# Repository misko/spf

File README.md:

# SPF (Signal Processing Fun)

## Youtube explanation

[Overview](https://www.youtube.com/watch?v=vj99KvB2AcA)

[Wall array v1 video](https://youtu.be/ljlRKGjBUoE) and [design+data+files](data_collection/2d_wall_array/2d_wall_array_v1)

[Wall array v2 video](https://youtu.be/9S3mgBD47kw) and [design+data+files](data_collection/2d_wall_array/2d_wall_array_v2)

[Rover v1 video](https://youtu.be/aGzOBduHrvo) and [design+data+files](data_collection/rover/rover_v1)

[Rover v2 video](https://youtube.com/shorts/qZmtBzATahE?feature=share) and [design+data+files](data_collection/rover/rover_v2)

Rover v3.1 [design+data+files](data_collection/rover/rover_v3.1)

## Problem statement:

Given a mobile radio receiver (agent/detector) find the optimal (minimal) path of movement to accurately locate physical radio emitters in the operating space

*(top left): The physical X,Y location of 3 static (non-mobile) emitters and one mobile detector (radio receiver). (top right): The raw radio signal from each antenna in the receiver radio array is [processed](spf/notebooks/03_beamformer_wNoise.ipynb) to produce a mapping from angle of incidence to signal strength. The larger the signal strength the more likely the signal originated from the corresponding angle. (bottom left): The ground truth the detector should output over enough time has elapsed. This represents the probability of finding an emitter at any X/Y coordinate. (bottom right): The processed radio signal from (top right) mapped into an image centered around the detectors position.*

## Background:

### The Challenge of Drone Detection

Detecting and locating small drones is increasingly important for security and airspace management. Traditional detection methods face significant challenges:

- Modern drones are small and becoming smaller
- Drones are often made from materials that don't reflect radar effectively
- Their extreme mobility makes tracking difficult with conventional systems

Most drones rely on radio frequency (RF) signals to communicate with operators, transmitting telemetry data and receiving commands. This RF communication provides an opportunity for detection even when visual or radar methods fail.

### Project Approach

This project develops optimal control algorithms for mobile radio receivers to locate RF emitters (such as drones) in an operational area. Key aspects of our approach:

1. **Mobile Detection**: Using airborne or ground-based mobile radio receivers that can dynamically position themselves for optimal signal reception
2. **Signal Integration**: Combining multiple signal measurements over time to build accurate emitter location maps
3. **Path Optimization**: Finding minimal movement paths that maximize information gain about emitter locations

### Technical Implementation

The system works by collecting and processing RF signals over time:

- **Signal Snapshots**: The receiver captures radio signals at discrete time intervals (snapshots)
- **Beamforming**: Raw antenna array data is processed through a [beamformer](spf/notebooks/03_beamformer_wNoise.ipynb) to map signal strength to angle of incidence
- **Spatial Mapping**: Processed signals are projected into a 2D probability map centered on the detector
- **Integration**: Multiple snapshots are combined to improve accuracy and reduce noise

The example below shows a single snapshot from our system. The blue circle represents the detector's position (with its path shown as a tail), while red circles mark emitter locations. The yellow areas in the bottom right image indicate high probability regions where an emitter is likely located based on the current signal processing.

## Current Progress

### Signal Processing & Algorithms

The project has implemented several sophisticated algorithms for emitter detection and localization:

#### Filtering Techniques
- **Extended Kalman Filters (EKF)**: Multiple implementations available in `spf/filters/`:
  - Single radio configuration (`ekf_single_radio_filter.py`)
  - Dual radio setup for improved accuracy (`ekf_dualradio_filter.py`)
  - XY coordinate tracking variants (`ekf_dualradioXY_filter.py`)

- **Particle Filters**: Probabilistic approach for robust tracking in noisy environments:
  - Single and dual radio implementations (`particle_single_radio_filter.py`, `particle_dualradio_filter.py`)
  - Neural network enhanced variants (`particle_single_radio_nn_filter.py`, `particle_dual_radio_nn_filter.py`)
  - XY coordinate variants for direct position estimation (`particle_dualradioXY_filter.py`)

#### Motion Planning
- Path planning algorithms in `spf/motion_planners/`:
  - Vehicle dynamics modeling (`dynamics.py`)
  - Optimal trajectory planning (`planner.py`)

#### Neural Network Models
- Advanced deep learning architectures in `spf/model_training_and_inference/models/`:
  - Point-based networks for signal processing (`single_point_networks.py`)
  - Optimized inference implementations (`single_point_networks_inference.py`) 
- Multiple model configurations in the `model_configs/` directory with variations in:
  - Network architecture (single vs. paired)
  - Regularization techniques (dropout, weight decay)
  - Training strategies (data augmentation, normalization)

### Data Collection & Hardware

#### Data Collection Systems
- **Wall-mounted Arrays**:
  - Fixed position antenna arrays for controlled experiments
  - Multiple versions (v1, v2) with different configurations

- **Mobile Platforms**:
  - Rover-based systems for dynamic data collection (v1, v2, v3.1)
  - Movement controlled via GRBL (`spf/grbl/`) or MAVLink (`spf/mavlink/`)
  - Flying drone platforms in experimental phase

#### Hardware Integration
- **SDR Support**:
  - **PlutoSDR** integration (`spf/sdrpluto/sdr_controller.py`)
  - **BladeRF 2.0** integration (`spf/sdrpluto/sdr_controller.py` with the `BladeRFSdr` class)
    - Advanced register-level configurations for phase alignment between channels
    - Support for multiple receivers with serial number identification
  - Signal processing and detrending utilities (`detrend.py`)
  - Abstracted hardware interfaces that work across SDR platforms

- **GPS Integration**:
  - Geolocation utilities (`spf/gps/gps_utils.py`)
  - Boundary definition for operation areas (`spf/gps/boundaries.py`)
  - Support for geofencing and automatic boundary detection

#### Drone Control
- **MAVLink Protocol**:
  - Advanced drone control interface (`spf/mavlink/mavlink_controller.py`)
  - Parameter management (`mavparm.py`)
  - Telemetry collection (`mavlink_radio_collection.py`)
  - Support for both real and simulated drones with the same API
  - Safety features including return-to-home functionality

### Dataset Management & Visualization

- **Dataset Generation & Processing**:
  - Custom dataset implementations (`spf/dataset/spf_dataset.py`)
    - Support for multiple SDR devices (PLUTO, BLADERF2, SIMULATION)
    - Data augmentation (flipping, striding, etc.)
  - Segmentation algorithms (`spf/dataset/segmentation.py`)
  - Synthetic data generation (`spf/dataset/fake_dataset.py`)

- **Analysis Tools**:
  - Extensive notebook collection in `spf/notebooks/` for:
    - Beamformer verification
    - Filter development and testing
    - Data visualization
    - Performance analysis

- **Evaluation Reports**:
  - Results tracked in `reports/` directory with multiple iterations
  - Analysis pipelines for algorithm comparison

### Cloud & Infrastructure

- **AWS Integration**:
  - S3 utilities for data storage and retrieval (`s3_utils.py`)
  - Cloud-based model training

- **Docker Support**:
  - Containerized development and deployment
  - Reproducible environments

## Test Suite

The project includes comprehensive testing to ensure reliability of all components:

### Signal Processing Tests
- **Beamformer Tests** (`test_beamformer.py`): Verifies beamforming algorithms for both uniform linear arrays (ULA) and uniform circular arrays (UCA) across multiple signal conditions
- **Segmentation Tests** (`test_beamformer.py`): Validates signal segmentation algorithms that identify continuous signal windows with stable phase relationships
- **Circular Mean Tests** (`test_beamformer.py`): Ensures accuracy of circular statistics used for angle estimation

### Filter Tests
- **Particle Filter Tests** (`test_particle_filter.py`): Tests single and dual radio particle filter implementations, including:
  - Single theta tracking with single radio
  - Single theta tracking with dual radio
  - XY-coordinate tracking with dual radio
- **EKF Tests** (`test_ekf.py`): Validates Extended Kalman Filter implementations for emitter tracking

### Motion Planning Tests
- **Dynamics Tests** (`test_dyanmics_and_planners.py`): Verifies vehicle dynamics models for both GRBL and GPS-based systems
- **Bounce Planning Tests** (`test_dyanmics_and_planners.py`): Tests the bounce trajectory planning algorithm to ensure efficient area coverage
- **GRBL Tests** (`test_grbl.py`): Detailed testing of the GRBL motion control system:
  - Coordinate transformations (steps to/from real-world coordinates)
  - Movement boundaries and collision avoidance
  - Simple move and bounce motion patterns
  - Radio collection during movement

### Hardware Integration Tests
- **MAVLink Tests** (`test_in_simulator.py`): Tests drone control via MAVLink in a simulated environment:
  - GPS time and boot time retrieval
  - Parameter loading and verification
  - Mode setting (manual, guided)
  - Drone movement commands
  - Signal recording during movement
- **GRBL Radio Collection Tests** (`test_grbl.py`): Tests collection of radio signals while using GRBL motion control

### Data Processing Tests
- **GPS Conversion Tests** (`test_gps.py`): Validates GPS coordinate processing, including:
  - GPS circle generation and bearing calculations
  - GPS to XY coordinate conversion
- **Dataset Tests** (`test_dataset.py`): Tests dataset creation and manipulation:
  - Data generation
  - Ground truth validation
  - Live data generation
  - V4 and V5 dataset format compatibility
- **Zarr Tools Tests** (`test_zarr_tools.py`): Validates zarr-based data storage operations
  
### Other Specialized Tests
- **Model Tests** (`test_models.py`, `test_new_models.py`): Verifies neural network model implementations
- **Rotation Distribution Tests** (`test_rotate_dist.py`, `test_paired_rotate_dist.py`): Tests rotation-based data augmentation
- **Fake Data Tests** (`test_fake_data.py`): Validates synthetic data generation
- **Invariance Tests** (`test_invariance.py`): Tests invariance properties of models to various transformations

## FAQ 

### Why use an airborne radio receiver?

To avoid multipath issues and noise from ground-based sources. Airborne receivers have a clearer line of sight to emitters and experience less signal reflection and interference from buildings, terrain, and other obstacles.

### What is a radio receiver in this context?

It can be any array of antenna receivers configured to a tunable radio so that the agent can scan across frequencies. In the current simulation setup, the array can be simulated as any number of linear or circular elements and processed through a relatively simple beamformer algorithm to produce the map of angle to signal strength required for input.

### What frequency bands does the system operate in?

The system is flexible and can be configured for different frequency bands. Current implementations primarily focus on 2.4 GHz (common for drone communications) but the architecture supports other frequencies that the SDR hardware can tune to.

### What's the difference between the different filter methods?

- **Extended Kalman Filters (EKF)** provide optimal state estimation when the system dynamics and measurement models are approximately linear and noise is Gaussian. They're computationally efficient but can fail with highly non-linear systems.
- **Particle Filters** use a set of weighted samples (particles) to represent the probability distribution of the state estimate. They're more robust to non-linearities and non-Gaussian noise but typically require more computational resources.
- **Neural Network Enhanced Filters** combine traditional filtering approaches with learned components to better handle complex signal environments and improve tracking accuracy.

### Can the system track multiple emitters simultaneously?

Not yet, soon.

### What are the hardware requirements for running the system?

For basic simulation and algorithm development:
- A standard computer with at least 8GB RAM
- Python 3.10 or newer
- CUDA-compatible GPU (optional, but recommended for neural network training)

For hardware deployment:
- SDR hardware (PlutoSDR or BladeRF 2.0)
- Mobile platform (rover or drone)
- Raspberry Pi or similar embedded computer for onboard processing
- GPS module for outdoor deployments

### How does the data format work?

The project uses Zarr arrays stored in LMDB databases for efficient data storage and access. The data format has evolved through several versions (currently v5) with enhancements for better performance and features. Each dataset contains:
- Raw IQ samples from the radio
- Metadata about detector position and orientation
- Signal processing results
- Ground truth information (for simulated data)

## Installation

### Software Setup

#### For Ubuntu/Debian Linux:

```bash
# Install system and SPF libiio build dependencies
sudo apt-get install -y git screen vim python3-dev python3-venv uhubctl \
  libusb-dev libusb-1.0-0-dev sshpass cmake make pkg-config flex bison \
  libxml2-dev libaio-dev

# Create and activate Python virtual environment
python3 -m venv spf_venv
source spf_venv/bin/activate

# Install the package in development mode
pip install -e .

# Install the hardware-qualified modified C library and Python binding last
./install_spf_libiio_artifacts.sh \
  --bundle ~/Downloads/spf-libiio \
  --python "$VIRTUAL_ENV/bin/python"

# Run the tests to verify installation
pytest tests
```

The modified libiio is required for v5 frame metadata; PyPI `pylibiio` alone
is not sufficient. CI publishes native Debian 12 packages for Pi 4/Pi 5
(`arm64`) and standard x86-64 (`amd64`), plus the shared Python wheel. The
source-building `install_spf_libiio.sh` remains available as a fallback. See
[the SPF libiio installation guide](docs/libiio_frame_metadata_install.md)
for immutable source pins, 0.26 instructions, verification, and isolated
side-by-side installs.

### Hardware Setup

#### PlutoSDR Setup:

1. Connect your PlutoSDR to your computer via USB
2. Verify the connection:
   ```bash
   iio_info -s
   ```
3. Configure the PlutoSDR (if needed):
   ```bash
   python -m spf.sdrpluto.sdr_controller --setup
   ```

#### BladeRF 2.0 Setup:

1. Install the BladeRF libraries and Python bindings:
   ```bash
   # Clone the BladeRF repository
   git clone --depth 1 https://github.com/Nuand/bladeRF.git
   
   pushd bladeRF/host
   mkdir build && cd build
   cmake ..
   make
   sudo make install
   sudo ldconfig
   popd 

   # Install the Python bindings
   cd bladeRF/host/libraries/libbladeRF_bindings/python
   python setup.py install
   ```

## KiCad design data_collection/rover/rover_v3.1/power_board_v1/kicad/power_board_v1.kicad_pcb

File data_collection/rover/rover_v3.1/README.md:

# 2D electric rover (v3.1)

Instead of simulations we can collect real world data by moving several rovers around autonomously in a field. Some rovers will transmit and others will listen and collect data.

## Operator documentation

- [Pre-field acceptance checklist](./PRE_FIELD_CHECKLIST.md) — mandatory
  release-level, per-Rover, real-radio Zarr, fake-drone, SITL, and restrained
  physical gates.
- [Full Rover operational runbook](./ROVER_RUNBOOK.md) — provisioning,
  operation, safety, troubleshooting, and recovery details.
- [Direct-USB gain/RSSI firmware runbook](../../../docs/direct_usb_gain_benchmark.md)
  — experimental RAM-boot firmware build, smoke, capture, validation, and
  rollback.
- [`load_direct_usb_firmware.sh`](./load_direct_usb_firmware.sh) — downloads
  the published checksum-pinned image, backs up the attached Pluto, performs a
  single-radio RAM boot, verifies it, and rolls back to QSPI.

## Design

Youtube [link](https://youtu.be/6D6IM0DY81c)

Youtube (mission) [link](https://youtu.be/8VCVYs3H9HY)

## Construction

### Antenna labels and physical alignment

Each radio drives a 2-element linear array; the elements are labelled by radio
letter + element index:

| Label | Radio | Element | Physical position |
|---|---|---|---|
| **A0** | A (USB2) | 0 | **starboard** |
| **A1** | A (USB2) | 1 | **port** |
| **B0** | B (USB1) | 0 | **bow** (forward) |
| **B1** | B (USB1) | 1 | **stern** (aft) |

So **array A lies athwartships** (starboard→port) and **array B lies fore-aft**
(bow→stern) — the two arrays are mounted 90° apart, which is exactly the
`theta-in-pis: 0` (radio A) / `theta-in-pis: 0.5` (radio B) pair in the capture
configs. Fusing the two differently-oriented arrays is what resolves the
front/back ambiguity of a 2-element array.

When cabling, element index = the Pluto RX channel (0 → RX1, 1 → RX2), so
A0/B0 go to RX1 and A1/B1 go to RX2 on their respective radio. Getting this
swapped flips the sign of the measured phase difference (an apparent mirror of
the bearing) without producing any obvious error at capture time — check it
against the labels above during the
[pre-field checklist](./PRE_FIELD_CHECKLIST.md) cabling step.

### GPS cable routing

Very sensitive to noise from pi + SDR , route it away from the inside!

### Flash rpi firmware

### Low power disconnect programming

```
press up to 5s +
press hold set 5s
use up down to set UP to 11.2v
press set
use up down to set DOWN to 11.1v
```

### Cytron Motor driver

Pins 3,4,6 set to high(1) rest to 0

MRB / MRA -> A motors
MLB / MLA -> B motors

### Battery compartment

Velcro include pictures

### USB port setup

```

USB  4     |     USB 3

USB  2   (Radio A)  |     USB 1 (Radio B)

Ethernet

```

### Ardupilot flash

Use mission planner windows
RPi script installs Arudpilot settings!

### PI setup

```
setup.sh
```

Get temperature

```
vcgencmd measure_temp
```

### Flash PlutoPlus

### SikRadio

[screen shot](./sikradio.jpg)
https://www.youtube.com/watch?v=i5lE2cWJJhM
Connect using mission planner
Set different NetIDs for each pair
Make sure to copy over settings
```
Rover 1 -> NetID 25
Rover 2 -> NetID 32
Rover 3 -> NetID 39
```

### Ardupilot calibration

Load base parameters

Accel calibration
Compass calibration
Change SYSID_THISMAV

Backup parameters

### Taranis Q setup

> **Superseded (2026-08-04) — the RF module and receiver below are no longer what flies.**
> The transmitter now runs the **R9M module in the external bay on ACCESS**, with an **R9 SX**
> receiver in each rover; internal XJT/D16 and the X8R are the original Jun-2024 link. The
> bind procedure in this section (F/S-button hold, red/green LED states) is the **ACCST/X8R**
> procedure and does **not** apply to an ACCESS R9 SX, which registers and binds from the
> module menu instead. Per-rover RxNums — Rover1 `01`, Rover2 `05`, Rover3 `00` — and the
> current bind state are in [`ROVER_RUNBOOK.md`](./ROVER_RUNBOOK.md) §3.5.1. The channel
> assignments further down this section are still broadly right, but §3.5.2 is authoritative.

```
Setup (Internal RF)
XJT D16
Ch Range CH1-16

Binding
(change receiver #) and have previous drones online to make sure we dont over bind the channel
With receiver off, hold down F/S button, power on while holding, let go 1 second later
Solid green/red -> no connection
Press bind on controller, beeping starts
Flashing green/red -> connection established
Reset receiver
Press ok on controller
Try moving around controller sticks to see X8R light go green

Input 1 -> 100 Rud
Input 2 -> 100 Ele
Input 3 -> 100 Thr
Input 4 -> 100 Alie

CH 1 -> 100 Ail
CH 2 -> 100 Ele
CH 3 -> 100 Thr
CH 4 -> 100 Rud
CH 5 -> 100 SF -> Arm [ Disarm, Arm ]
CH 6 -> 100 S2
CH 7 -> 100 SD
CH 8 -> 100 SA -> Flight mode [ Manual , Guided, RTL ]
CH 9 -> 100 SH -> Shutdown [ Momentary -> shutdown ]
CH 10 -> 100 SC -> Mag calibration [ Nothing, Mag cal, Nothing ]

```

> **Correction (2026-07-23):** with the boot-enforced ArduPilot params
> (`rover3_base_parameters.params`: `MODE_CH 8`, `MODE4=11` RTL, `MODE6=15` Guided),
> the SA flight-mode positions are **[ Manual, RTL, Guided ]** — Guided/RTL are swapped
> relative to the list above. The list above also omits CH7 (SD = reboot FC / kill
> collector) and CH12 (ultrasonic on/off), which the Pi consumes. Full current control
> map: [`ROVER_RUNBOOK.md`](./ROVER_RUNBOOK.md) §3.5 and `taranis_q_controls.png`.

To swap throttle from the left to the right , 

```

Originally set to
CH1 = Ail
CH2 = Ele
CH3 = Thr
CH4 = Rud

Go to MIXES on controller and set to 
CH1 = Rud
CH2 = Thr
CH3 = Ele
CH4 = Ail

```

### 3D printed parts

- [Versioned seven-antenna mount and flat-base STLs](./3D_printed_parts/antenna_mount/README.md)
  — 47.5 mm and 51 mm antenna pitch-circle diameters, plus an E-Z LOK insert
  base for standalone mounting.
- [Parametric source and dimensional validation](../../3D_printing_design_files/antenna_mount.md)
  — regenerate the mounts or select a different spacing.
- [Legacy Rover v3 parts archive](https://www.dropbox.com/s/egpfn434aox6vvk/roverv3_3dparts.zip?dl=0)
  — pre-existing Rover v3 printable parts.

## Lab checks

Use the mandatory, current commands and pass/fail criteria in the
[pre-field acceptance checklist](./PRE_FIELD_CHECKLIST.md). The snippets below
are ad hoc diagnostics, not field-readiness evidence.

### SDR

Emit from an SDR

```
python sdr_controller.py --emitter-uri ip:192.168.1.15 --receiver-uri ip:192.168.1.17 --mode tx  --fc 2467000000
```

Receive frmo an SDR

```
python sdr_controller.py --receiver-uri usb:2.11.5 --mode rx --fc 2500000000 --rx-mode fast_attack
```

Use a fake drone and the current Rover 3 production configuration to receive
100 frames per configured physical radio:

```
/home/pi/spf-virtualenv/bin/python3 spf/mavlink_radio_collection.py \
  -c data_collection/rover/rover_v3.1/capture_configs/rover_receiver_config_pi_3mhz_43mm.yaml \
  -m ~/device_mapping -r center --fake-drone --no-ultrasonic -n 100
```

Rover 1 and Rover 2 use different production configs. Select them from the
per-Rover table in the checklist rather than reusing the Rover 3 example.

Use a fake drone and the emitter bench configuration to emit and receive:

```
/home/pi/spf-virtualenv/bin/python3 spf/mavlink_radio_collection.py \
  -c data_collection/rover/rover_v3.1/capture_configs/rover_emitter_config_pi_simulator.yaml \
  -m ~/device_mapping -r center --fake-drone --no-ultrasonic -n 100
```

For ArduPilot SITL, use the [MAVLink simulator instructions](../../../spf/mavlink/README.md)
and the release-level gate in the pre-field checklist.

## devpi mission control

```
#rover1
mavproxy.py --master /dev/serial/by-id/usb-FTDI_FT230X_Basic_UART_DK0G4IOK-if00-port0 

#rover2
mavproxy.py --master /dev/serial/by-id/usb-FTDI_FT230X_Basic_UART_DK0G4W25-if00-port0 

#rover3
mavproxy.py --master /dev/serial/by-id/usb-FTDI_FT230X_Basic_UART_DK0G5WCE-if00-port0
```

## Flash ESP32

```

arduino-cli core update-index

```

## debug
```
/home/pi/spf-virtualenv/bin/python3 ${repo_root}/spf/mavlink_radio_collection.py -c ${config} -m ~/device_mapping --fake-drone -r center -n 4000
```

## Missions

### Lab check

### Mission 1

## PDFs

[GoBilda recon](https://www.dropbox.com/scl/fi/ks1fxsgilpyjsh96b6yut/gobilda_recon_assembly.pdf?rlkey=jf0m082piixa4lvxsqi4eruph&dl=0)

[Low power disconnect](https://www.dropbox.com/scl/fi/wmjql1251xnxs90oqn2jd/lower_power_disconnect_30A.pdf?rlkey=h3vitle22f5xrkcthws3yf8ft&dl=0)

[Cytron Smart duo 30](https://www.dropbox.com/scl/fi/eeqg87gi8wzy2aa1k1yx3/MDDS30_User_Manual.pdf?rlkey=xe49gu88bpqspxbg2dh6x139w&dl=0)

[Fans](https://www.dropbox.com/s/b4bna0s1yyfwyqa/cooler_guys_fan.pdf?dl=0)

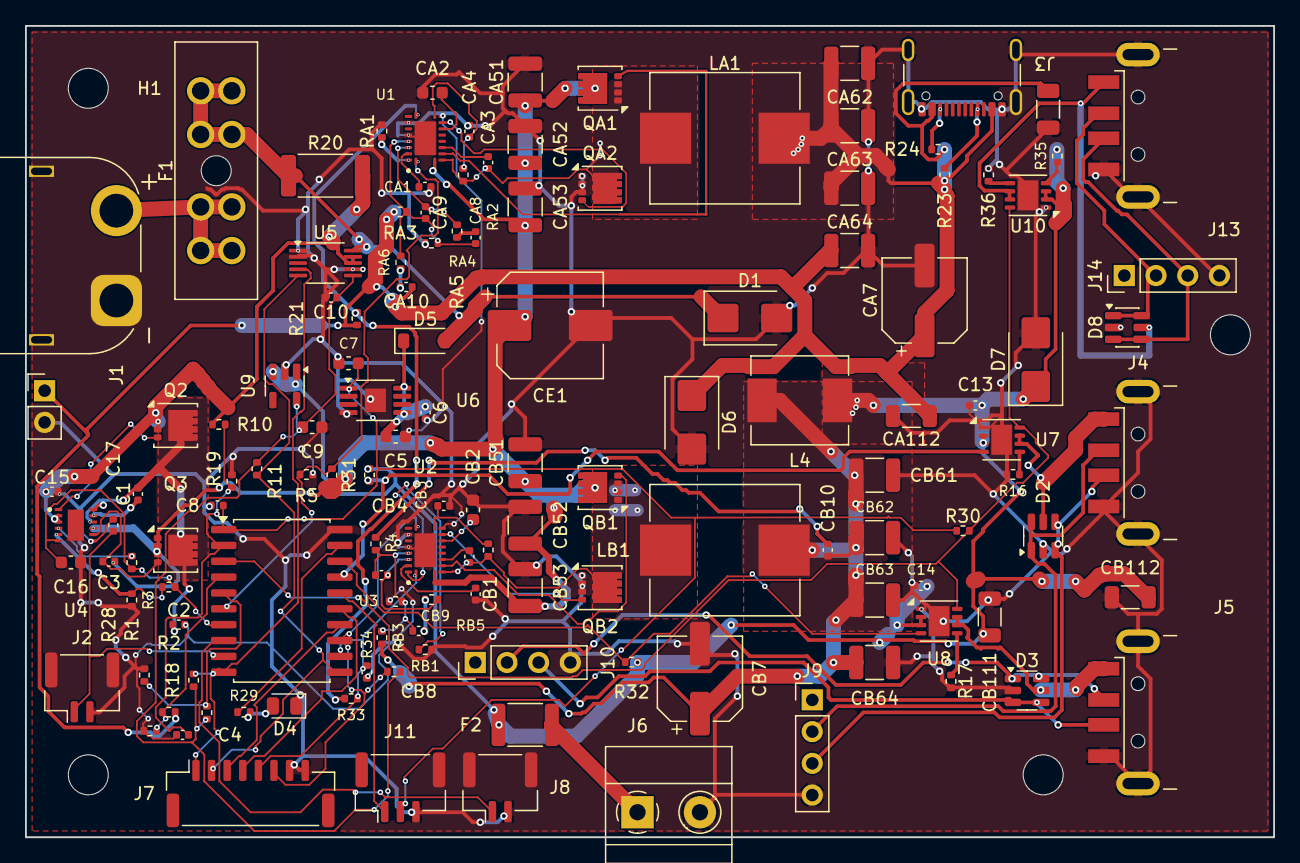
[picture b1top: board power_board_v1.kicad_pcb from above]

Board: 4 copper layers, 100.0 x 65.0 mm, 137 parts (0 on the bottom side), 77 nets.

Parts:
C1: 100n CAP-VS; C_0402_1005Metric
C2: 100n VS-GND; C_0402_1005Metric
C3: 47n HGATE dv/dt (10ms); C_0402_1005Metric
C4: 100n vsense hold; C_0402_1005Metric
C5: 1u LDO in; C_0603_1608Metric
C6: 100n LDO in; C_0402_1005Metric
C7: 2u2 LDO out; C_0603_1608Metric
C8: 100n MCU vdd; C_0402_1005Metric
C9: 1u LDO out; C_0603_1608Metric
C10: 100n INA vs; C_0402_1005Metric
C13: 100n U7 in; C_0402_1005Metric
C14: 100n U8 in; C_0402_1005Metric
C15: 100n at U4.A; C_0402_1005Metric
C16: 2u2 EN delay; C_0603_1608Metric
C17: 100n sw debounce; C_0402_1005Metric
CA1: 47n SS (4ms); C_0402_1005Metric
CA2: 2u2 VCC; C_0603_1608Metric
CA3: 100n BST; C_0402_1005Metric
CA4: 18p CILIM; C_0402_1005Metric
CA7: 220u poly 25mR; CP_Elec_6.3x5.9
CA8: 8n2 CC1; C_0402_1005Metric
CA9: 39p CC2; C_0402_1005Metric
CA10: 1n2 CC3; C_0402_1005Metric
CA51, CA52, CA53: 10u 50V X7R; C_1210_3225Metric
CA61, CA62, CA63, CA64: 47u 10V X7R; C_1210_3225Metric
CA111, CA112: 22u local; C_1206_3216Metric
CB1: 47n SS (4ms); C_0402_1005Metric
CB2: 2u2 VCC; C_0603_1608Metric
CB3: 100n BST; C_0402_1005Metric
CB4: 18p CILIM; C_0402_1005Metric
CB7: 220u poly 25mR; CP_Elec_6.3x5.9
CB8: 8n2 CC1; C_0402_1005Metric
CB9: 39p CC2; C_0402_1005Metric
CB10: 1n2 CC3; C_0402_1005Metric
CB51, CB52, CB53: 10u 50V X7R; C_1210_3225Metric
CB61, CB62, CB63, CB64: 47u 10V X7R; C_1210_3225Metric
CB111, CB112: 22u pi-out; C_1206_3216Metric
CE1: 100u hybrid 25V; CP_Elec_8x10
D1: SMBJ16A; D_SMB
D2, D3, D8: USBLC6-2SC6; SOT-23-6
D4: green status; LED_0805_2012Metric
D5: B5819W schottky; D_SOD-123
D6, D7: SMBJ5.0A; D_SMB
F1: 15A ATO; FuseHolder_Blade_ATO_Littelfuse_FLR_178.6165
F2: 2A polyfuse; Fuse_1812_4532Metric
H1, H2, H3, H4: MountingHole_3.2mm_M3
J1: XT60_BATT; AMASS_XT60PW-M_1x02_P7.20mm_Horizontal
J2: PANEL_SW; JST_GH_BM02B-GHS-TBT_1x02-1MP_P1.25mm_Vertical
J3: USB4105-GF-A (TH shell); USB_C_Receptacle_GCT_USB4105-xx-A_16P_TopMnt_Horizontal
J4: USB_A radio1; USB_A_CNCTech_1001-011-01101_Horizontal
J5: USB_A radio2; USB_A_CNCTech_1001-011-01101_Horizontal
J6: AUX 5V 2A; TerminalBlock_Phoenix_MKDS-1,5-2_1x02_P5.00mm_Horizontal
J7: PI GPIO harness; JST_GH_SM08B-GHS-TB_1x08-1MP_P1.25mm_Horizontal
J8: AUX_CTL out (JST-GH); JST_GH_BM02B-GHS-TBT_1x02-1MP_P1.25mm_Vertical
J9: from Pi USB1; PinHeader_1x04_P2.54mm_Vertical
J10: from Pi USB2; PinHeader_1x04_P2.54mm_Vertical
J11: UPDI prog (UPDI/3V3/GND); JST_GH_BM03B-GHS-TBT_1x03-1MP_P1.25mm_Vertical
J12: 5V_A pigtail (DNP); PinHeader_1x02_P2.54mm_Vertical
J13: USB_A port3 (3A); USB_A_CNCTech_1001-011-01101_Horizontal
J14: from Pi USB3; PinHeader_1x04_P2.54mm_Vertical
L4: pi-filter 1u; L_Chilisin_BMRx00060630
LA1: MWSA1005S-3R3 16A; L_Sunlord_MWSA1005S
LB1: MWSA1005S-3R3 16A; L_Sunlord_MWSA1005S
Q2: CSD18543Q3A diode; VSON-8_3.3x3.3mm_P0.65mm_NexFET
Q3: CSD18543Q3A switch; VSON-8_3.3x3.3mm_P0.65mm_NexFET
QA1: CSD18543Q3A HS; VSON-8_3.3x3.3mm_P0.65mm_NexFET
QA2: CSD18543Q3A LS; VSON-8_3.3x3.3mm_P0.65mm_NexFET
QB1: CSD18543Q3A HS; VSON-8_3.3x3.3mm_P0.65mm_NexFET
QB2: CSD18543Q3A LS; VSON-8_3.3x3.3mm_P0.65mm_NexFET
R1: 887k ladder-top; R_0402_1005Metric
R2: 28k7 ladder-mid; R_0402_1005Metric
R3: 82k5 ladder-bot; R_0402_1005Metric
R4: 100k EN-A hi (8.5V on); R_0402_1005Metric
R5: 16k5 EN-A lo (7.5V off); R_0402_1005Metric
R10: 680k vsense-hi; R_0402_1005Metric
R11: 100k vsense-lo; R_0402_1005Metric
R16: 20k RILIM1 (~3A); R_0402_1005Metric
R17: 20k RILIM2 (~3A); R_0402_1005Metric
R18, R19: 4k7 I2C pu (3V3_SW); R_0402_1005Metric
R20: 2m 3W shunt; R_2512_6332Metric
R21: 20k PGOOD_A pu (5V_A); R_0402_1005Metric
R22: 10k PGOOD_B pu (3V3_SW); R_0402_1005Metric
R23, R24: 10k Rp (3A adv); R_0402_1005Metric
R25: 30k v5a-hi; R_0402_1005Metric
R26: 10k v5a-lo; R_0402_1005Metric
R27: 10k NTC-top (3V3_SW); R_0402_1005Metric
R28: 10k NTC 3380K; R_0402_1005Metric
R29: 1k LED; R_0402_1005Metric
R30: 10k FAULT pu; R_0402_1005Metric
R31: 100k EN1 pu (5V_B); R_0402_1005Metric
R32: 100k EN2 pu (5V_B); R_0402_1005Metric
R33: 20k seq div hi; R_0402_1005Metric
R34: 16k5 seq div lo; R_0402_1005Metric
R35: 100k EN3 pu; R_0402_1005Metric
R36: 20k RILIM3 (~3A); R_0402_1005Metric
RA1: 16k5 RT (606kHz); R_0402_1005Metric
RA2: 348R RILIM (wc-min 6.3A); R_0402_1005Metric
RA3: 20k RFB1; R_0402_1005Metric
RA4: 3k65 RFB2 (5.18V); R_0402_1005Metric
RA5: 13k RC1; R_0402_1005Metric
RA6: 4k64 RC2; R_0402_1005Metric
RB1: 16k5 RT (606kHz); R_0402_1005Metric
RB2: 348R RILIM (wc-min 6.3A); R_0402_1005Metric
RB3: 20k RFB1; R_0402_1005Metric
RB4: 3k74 RFB2 (5.08V); R_0402_1005Metric
RB5: 13k RC1; R_0402_1005Metric
RB6: 4k64 RC2; R_0402_1005Metric
U1: LM5145 rail A; VQFN-20_3.5x4.5_P0.5_LM5145RGY
U2: LM5145 rail B; VQFN-20_3.5x4.5_P0.5_LM5145RGY
U3: ATtiny1616-SN (816-compat); SOIC-20W_7.5x12.8mm_P1.27mm
U4: LM74800-Q1; WSON-12_3x3_P0.5_LM74800DRR
U5: INA226 (addr 0x40); VSSOP-10_3x3mm_P0.5mm
U6: TPS7A1633 3V3 60V LDO; MSOP-8-1EP_3x3mm_P0.65mm_EP1.68x1.88mm
U7, U8: TPS2557 ~3A; VSON-8-1EP_3x3mm_P0.65mm_EP1.65x2.4mm
U9: AP2112K-3.3 (switched); SOT-23-5
U10: TPS2557 ~3A (always on); VSON-8-1EP_3x3mm_P0.65mm_EP1.65x2.4mm

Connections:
3V3_SW: C9.1, C10.1, R18.1, R19.1, R22.1, R27.1, U5.6, U9.5
5VB_PRE: CB7.1, CB10.1, CB61.1, CB62.1, CB63.1, CB64.1, L4.1, LB1.2, RB3.1
5V_A: CA7.1, CA10.1, CA61.1, CA62.1, CA63.1, CA64.1, CA111.1, CA112.1, D6.1, J3.A4, J3.A9, J3.B4, J3.B9, J12.1, LA1.2, R21.1, R23.1, R24.1, R25.1, RA3.1
5V_B: C13.1, C14.1, CB111.1, CB112.1, D7.1, F2.1, L4.2, R31.1, R32.1, R35.1, U7.2, U7.3, U8.2, U8.3, U9.1, U9.3, U10.2, U10.3
AUX_5V: F2.2, J6.1
AUX_CTL: J8.1, U3.8
BST_A: CA3.1, U1.17
BST_B: CB3.1, U2.17
CC1_A: J3.A5, R23.2
CC2_A: J3.B5, R24.2
COMP_A: CA9.1, RA5.1, U1.4
COMP_B: CB9.1, RB5.1, U2.4
CX_A: CA8.1, RA5.2
CX_B: CB8.1, RB5.2
CY_A: CA10.2, RA6.1
CY_B: CB10.2, RB6.1
D1_N: D2.1, D2.6, J4.2, J9.2
D1_P: D2.3, D2.4, J4.3, J9.3
D2_N: D3.1, D3.6, J5.2, J10.2
D2_P: D3.3, D3.4, J5.3, J10.3
D3_N: D8.1, D8.6, J13.2, J14.2
D3_P: D8.3, D8.4, J13.3, J14.3
DG_FE: Q2.4, U4.1
EN_A: R4.2, R5.1, U1.1, U3.6
EN_USB1: R31.2, U3.17, U7.4
EN_USB2: R32.2, U3.18, U8.4
EN_USB3: R35.2, U10.4
FAULT_USB: R30.2, U3.3, U7.8, U8.8, U10.8
FB_A: CA8.2, CA9.2, RA3.2, RA4.1, RA6.2, U1.5
FB_B: CB8.2, CB9.2, RB3.2, RB4.1, RB6.2, U2.5
FE_CAP: C1.1, U4.11
FE_EN: C16.1, R1.2, R2.1, U3.7, U4.6
FE_LAD: R1.1, U4.4
FE_MID: C1.2, C2.1, Q2.5, Q3.5, U4.10, U4.12
FE_OV: R2.2, R3.1, U4.5
GND: C2.2, C4.2, C5.2, C6.2, C7.2, C8.2, C9.2, C10.2, C13.2, C14.2, C15.2, C16.2, C17.2, CA1.2, CA2.2, CA4.2, CA7.2, CA51.2, CA52.2, CA53.2, CA61.2, CA62.2, CA63.2, CA64.2, CA111.2, CA112.2, CB1.2, CB2.2, CB4.2, CB7.2, CB51.2, CB52.2, CB53.2, CB61.2, CB62.2, CB63.2, CB64.2, CB111.2, CB112.2, CE1.2, D1.2, D2.2, D3.2, D4.1, D6.2, D7.2, D8.2, J1.1, J2.2, J3.A1, J3.A12, J3.B1, J3.B12, J3.S1, J4.4, J4.5, J5.4, J5.5, J6.2, J7.7, J7.8, J8.2, J9.4, J10.4, J11.3, J12.2, J13.4, J13.5, J14.4, QA2.1, QA2.2, QA2.3, QB2.1, QB2.2, QB2.3, R3.2, R5.2, R11.2, R16.2, R17.2, R26.2, R28.2, R34.2, R36.2, RA1.2, RA4.2, RB1.2, RB4.2, U1.6, U1.8, U1.12, U1.21, U2.6, U2.8, U2.12, U2.21, U3.20, U4.7, U5.1, U5.2, U5.7, U6.4, U6.9, U7.1, U7.9, U8.1, U8.9, U9.2, U10.1, U10.9
HG_FE: C3.1, Q3.4, U4.8
HO_A: QA1.4, U1.18
HO_B: QB1.4, U2.18
ILIM1: R16.1, U7.5
ILIM2: R17.1, U8.5
ILIM3: R36.1, U10.5
ILIM_A: CA4.1, RA2.1, U1.11
ILIM_B: CB4.1, RB2.1, U2.11
LED_K: D4.2, R29.2
LED_STAT: R29.1, U3.19
LOW_BATT: J7.3, U3.14
LO_A: QA2.4, U1.13
LO_B: QB2.4, U2.13
MCU_3V3: C7.1, C8.1, J11.2, R30.1, U3.1, U6.1
NTC: R27.2, R28.1, U3.5
PGOODA_RAW: R21.2, R33.1, U1.10
PGOOD_A: J7.5, R33.2, R34.1, U2.1, U3.12
PGOOD_B: J7.6, R22.2, U2.10, U3.13
RT_A: RA1.1, U1.2
RT_B: RB1.1, U2.2
SCL: J7.2, R19.2, U3.11, U5.5
SDA: J7.1, R18.2, U3.10, U5.4
SHDN_ACK: J7.4, U3.15
SS_A: CA1.1, U1.3
SS_B: CB1.1, U2.3
SW_A: CA3.2, LA1.1, QA1.1, QA1.2, QA1.3, QA2.5, RA2.2, U1.19
SW_B: CB3.2, LB1.1, QB1.1, QB1.2, QB1.3, QB2.5, RB2.2, U2.19
SW_SENSE: C17.1, J2.1, U3.9
UPDI: J11.1, U3.16
V5A_SENSE: R25.2, R26.1, U3.4
VBATT_F: D1.1, D5.2, F1.2, R20.1, U5.10
VBATT_FD: C5.1, C6.1, D5.1, U6.5, U6.8
VBATT_RAW: F1.1, J1.2
VBATT_S: C15.1, Q2.1, Q2.2, Q2.3, R10.1, R20.2, U4.2, U4.3, U5.8, U5.9
VBUS1: D2.5, J4.1, U7.6, U7.7
VBUS2: D3.5, J5.1, U8.6, U8.7
VBUS3: D8.5, J13.1, U10.6, U10.7
VCC_A: CA2.1, U1.14
VCC_B: CB2.1, U2.14
VSENSE: C4.1, R10.2, R11.1, U3.2
VSW: C3.2, CA51.1, CA52.1, CA53.1, CB51.1, CB52.1, CB53.1, CE1.1, Q3.1, Q3.2, Q3.3, QA1.5, QB1.5, R4.1, U1.20, U2.20, U4.9

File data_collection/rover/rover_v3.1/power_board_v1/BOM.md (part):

# Power board v1 — BOM (P2 lockdown)

Status: **P2 LOCKED 2026-07-13** — every line has MPN + package + LCSC C# (or is a
commodity basic-lib value). Verified against LCSC/JLC by three parallel catalog
sweeps; stock/prices are point-in-time — re-check every C# in the JLCPCB BOM tool
at order placement (P5). Substitutions from the P1 design: LM25145→LM5145 (stock;
datasheet-verified equation-identical), SQJQ140E→2×CSD18543Q3A (stock/price),
ATtiny816 SOIC→UQFN (stock). RILIM recomputed for CSD18543Q3A (301/243 Ω).

Source of truth for values: P1_DETAIL_DESIGN.md §2 + kicad/generate_schematic.py v2.
Board qty assumption: 5 prototypes (JLCPCB assembly, P0 decision 4).

## A. Passives — resistors (all 0402 1% unless noted; JLC basic lib)
| Refs | Value | Qty/board | Note |
|---|---|---|---|
| R1 | 887 kΩ | 1 | LM74800 ladder top |
| R2 | 28.7 kΩ | 1 | ladder mid (EN tap) |
| R3 | 82.5 kΩ | 1 | ladder bottom (OV tap) |
| RA1, RB1 | 16.5 kΩ | 2 | RT (606 kHz) |
| R5 | 16.5 kΩ | 1 | buck A EN lo |
| R4, R10† | 100 kΩ / 680 kΩ† | 1+1 | EN hi; †VIN sense hi (680k) |
| R11 | 100 kΩ | 1 | VIN sense lo |
| RA2 | 301 Ω | 1 | RILIM A — recomputed for CSD18543Q3A 8.5 mΩ: 7.0 A valley × 0.0085 / 200 µA |
| RB2 | 243 Ω | 1 | RILIM B — 5.7 A valley × 0.0085 / 200 µA |
| RA3, RB3 | 20.0 kΩ | 2 | RFB1 |
| RA4, RB4 | 3.74 kΩ | 2 | RFB2 (5.08 V) |
| RA5, RB5 | 13.0 kΩ | 2 | RC1 comp |
| RA6, RB6 | 4.64 kΩ | 2 | RC2 comp |
| R16, R17 | 20.0 kΩ | 2 | TPS2553 RILIM (1.2 A) |
| R18, R19 | 4.7 kΩ | 2 | I2C pull-ups (MCU_3V3) |
| R21, R22, R27, R30 | 10.0 kΩ | 4 | PGOOD pu ×2, NTC top, FAULT pu |
| R23, R24 | 10.0 kΩ | 2 | USB-C Rp (3 A advertisement) |
| R25 | 30.0 kΩ | 1 | V5A sense hi |
| R26 | 10.0 kΩ | 1 | V5A sense lo |
| R29 | 1.0 kΩ | 1 | status LED |
| R28 | NTC 10 kΩ B3380 0603 | 1 | e.g. NCP18XH103F03RB-class (verify C#) |
| R20 | Milliohm HoSCG2512-3-R002-F-4, 2 mΩ 1 % 3 W 2512 | 1 | **C22450699** ($0.10, stock 2.9k); "-4" suffix suggests 4-terminal — verify land pattern from datasheet at P3; alt LR2512D-3W-2mR C500736 |

## B. Passives — capacitors (JLC basic lib)
| Refs | Value | Size | Qty/board | Note |
|---|---|---|---|---|
| C1, C2, CA3, CB3, C4 (+decoupling kit at P3) | 100 nF 50 V X7R | 0402 | 5+ | FE CAP/VS, BST ×2, VSENSE hold |
| C3 | 47 nF 50 V | 0402 | 1 | HGATE dv/dt (10 ms soft-start) |
| CA1, CB1 | 47 nF | 0402 | 2 | SS (4 ms) |
| CA2, CB2 | 2.2 µF 16 V X7R | 0603 | 2 | VCC LDO |
| CA4 | 18 pF C0G | 0402 | 1 | CILIM A (RC≈6 ns) |
| CB4 | 22 pF C0G | 0402 | 1 | CILIM B |
| CA5, CB5 | 10 µF 50 V X7R | 1210 | 6 | buck input (3 per rail) — FH 1210B106K500NT C116808 (JLC "Economic PCBA"); alts C3844168 / C77102 |
| CA6, CB6 | 47 µF 10 V X7R | 1210 | 8 | buck output ceramic (4 per rail) — Murata GRM32ER71A476KE15L C84494; alt TDK C76680 |
| CA11, CB11 | 22 µF 10 V X7R | 0805/1206 | 4 | pi-filter out (2 per rail) |
| CA8, CB8 | 8.2 nF X7R | 0402 | 2 | CC1 comp |
| CA9, CB9 | 39 pF C0G | 0402 | 2 | CC2 comp |
| CA10, CB10 | 1.2 nF X7R | 0402 | 2 | CC3 comp |
| CA7, CB7 | Lelon OCV221M0JTR-0606, 220 µF 6.3 V polymer | 6.3×5.9 SMD | 2 | **C250009** ($0.15, stock 4.8k). 5.1 V on 6.3 V = 81 % derating — acceptable for polymer (no MLCC-style DC bias loss) but prefer a 10 V part if one shows up in the JLC BOM tool; ESR ~20-25 mΩ (OCV series, unconfirmed — comp assumes 25 mΩ; bench Bode at P7 verifies) |

## C. Semiconductors — ICs VERIFIED vs LCSC 2026-07-13 (all Extended lib)
| Refs | Part | LCSC C# | Package | Stock | ~$ q10 | Notes |
|---|---|---|---|---|---|---|
| U1, U2 | **LM5145RGYR** | C485912 | VQFN-20 RGY | 400 | 2.18 | **substitution verified against LM5145 datasheet (SNVSAI4B)**: LM25145RGYR (C2876740) has only 7 pcs at LCSC. LM5145 (75 V) is equation-identical — RT=10⁴/Fsw, VREF 0.8 V, ISS 10 µA, kFF 15, ILIM 200 µA + 6 ns, same L/Cout eqs — so ALL computed values in P1_DETAIL_DESIGN.md §2 carry over unchanged |
| U4 | LM74800QDRRRQ1 | C3215600 | WSON-12 DRR | 1,935 | 1.58 | exact part; alt LM74801 (C2873366, 48 pcs) |
| U3 | **ATTINY816-SSNR** | C2054204 | SOIC-20W 1.27 mm | **VERIFY STOCK** | ~1.0 | **package changed back to SOIC 2026-07-14**: the UQFN's 0.4 mm pitch made its last 4-5 nets unroutable at any legal geometry (escape saturation); SOIC-20 routes fully. Same ports → firmware unchanged. C2054204 was zero-stock when UQFN was chosen — AT ORDER TIME verify LCSC stock; if still dry, substitute **ATTINY1616-SNR** (SOIC-20, pin-identical superset, more flash/RAM, firmware runs unmodified) or any tinyAVR 1-series x16 SOIC-20 |
| U5 | INA226AIDGSR | C49851 | VSSOP-10 | 11,139 | 0.69 | exact part |
| U6 | TPS7A1633DGNR | C181239 | MSOP-8 PwrPAD | 1,842 | 1.43 | exact part (60 V, 5 µA IQ); alt TPS7B6933 (C108471) only 40 V — keep TPS7A16 |
| U7, U8 | TPS2553DBVR | C55266 | SOT-23-6 | 39,155 | 0.32 | AUTO-RETRY version ✓ (do NOT sub C111738 = latching -1) |
| U9 | AP2112K-3.3TRG1 | C51118 | SOT-25 | 30,780 | 0.16 | Extended; basic-lib fallback AMS1117-3.3 (C6186) has no EN + 5 mA IQ — fine since rail is switched |
| Q2, Q3 | **2× CSD18543Q3A** (common-drain b2b) | C840100 | VSONP-8 3.3×3.3 | 1,040 | 0.65 | **substitution**: SQJQ140E is unobtainable (5 pcs @ $8.74). Same part as buck FETs — one feeder for all 6 FETs/board. VGS ±20 V ✓ vs LM74800's 13 V drive |
| QA1,QB1 / QA2,QB2 | CSD18543Q3A (HS+LS both rails) | C840100 | VSONP-8 | 1,040 | 0.65 | 60 V, 8.1 mΩ @10 V (~8.5 @7.5 V), Qg 11.1 nC. RILIM recomputed → 301/243 Ω. 30 pcs for 5 boards vs 1,040 stock ✓. Budget alt: TDM3436 C380232 (verify ±VGS ≥16 V before use) |
| D1 | SMBJ16A (Littelfuse) | C151254 | SMB | 5,255 | 0.13 | cheap alt YFW C2898407 |
| D2, D3 | USBLC6-2SC6 | C7519 | SOT-23-6 | ok | 0.10 | |
| D4 | KT-0805G green LED | C2297 | 0805 | ok | 0.01 | **Basic lib confirmed** |

## D. Magnetics — VERIFIED vs LCSC/JLC 2026-07-13
| Refs | Part | LCSC C# | Specs | Qty | Notes |
|---|---|---|---|---|---|
| LA1, LB1 | Sunlord MWSA1005S-3R3MT | C17700181 | 3.3 µH, Isat 16 A, DCR 10 mΩ, 11.5×10 mm | 2 | chosen for margin (OCP peak ≈8.6 A) + one feeder both rails; price TBD in JLC BOM tool. Fallback (rail B only): cjiang FXL0630-3R3-M C167219 (9.5 A/22 mΩ, 7×6.6, $0.17) |
| L2, L4 | cjiang FXL0630-1R0-M | C167216 | 1 µH, Isat 15 A, DCR 7.4 mΩ, 7×6.6 | 2 | $0.17; alt MPCA-0630-1R0 C268399 |

## E. Connectors / electromechanical — VERIFIED vs LCSC 2026-07-13
All TH connectors need JLCPCB hand-solder/wave add-on; all lines Extended
(≈$3 loader fee each). JLC-library stock can differ from LCSC retail — recheck
C#s in the JLC BOM tool at order time.

| Refs | Part | LCSC C# | Mount | ~$ q10 | Qty | Notes |
|---|---|---|---|---|---|---|
| J1 | AMASS XT60PW-M | C98732 | TH r/a | 0.39 | 1 | genuine AMASS |
| J12 | AMASS XT30PW-M30.G.Y | C431092 | TH r/a | 0.23 | 1 (DNP) | stock 5.4k |
| J3 | GCT USB4105-GF-A | C3020560 | SMD pins + **TH shell tabs** | 0.55 | 1 | 16P, CC1/CC2 exposed; strain relief ✓ (alt: SHOU HAN C2765186 $0.07 but shell-tab style unverified) |
| J4, J5 | Jing Ext. 901-211A1021D10100 USB-A | C2345 | TH r/a | 0.04 | 2 | classic cheap TH |
| J7 | JST SM08B-GHS-TB (8-pin GH, **side-entry**) | C265111 | SMD | 0.44 | 1 | Pixhawk-standard horizontal; if top-entry wanted: BM08B-GHS-TBT (C# unverified) — decide at P3 vs harness routing |
| J2, J8 | JST BM02B-GHS-TBT (2-pin GH, top) | C161690 | SMD | 0.12 | 2 | genuine JST |
| J11 | JST BM03B-GHS-TBT (3-pin GH, top) | C161691 | SMD | 0.43 | 1 | stock 2.3k |
| J9, J10 | 2.54 4-pin header (Pi USB passthrough) | basic-lib generic | TH | 0.02 | 2 | or captive pigtail at P3 |
| F1 | Keystone 3557-10 ATO holder | C3205403 | TH | 1.70 | 1 | **stock only 383** — alt MPD BF353 C3206285 |
| F1 fuse | Littelfuse 0257015.PXPV ATO 15 A | C142692 | blade | 0.05 | 1 | NOT 0287015 (that's MINI blade) |
| CBL1 | Silkland 0.5 ft 240 W USB-C cable, ASIN B0CQ4SX256 | — (Amazon) | — | ~10 | 1/rover | P0 decision 3 |

## F. Cost estimate @ qty 5 (LCSC point-in-time prices)
Parts/board: ICs ~$9.6 (2×LM5145 4.36, LM74800 1.58, tiny816 0.70, INA226 0.69,
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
